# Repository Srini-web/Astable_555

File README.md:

# Astable Vibrator using NE555 timer module
The design of an astable vibrator using the Autodesk Eagle software. The module is designed using the NE555 timer module. It also features an external Voltage regulator to filter out the 5 to 5.5 voltage received. The interface primarily features:

+ STM-NE555 timer
+ LM7805 fixed voltage IC regulator
+ DCJ0202 DC power jack (2.1mm)

These are followed by other basic electronic components like resistors, Capacitors, and LEDs.

## Schematic
The schematic design includes all the elements of the astable vibrator circuit including a pull-up circuit for the input voltage.

### ERC

## Placement (Layout)

## Routing

#### Groundpour

### DRC

## Manufacture View

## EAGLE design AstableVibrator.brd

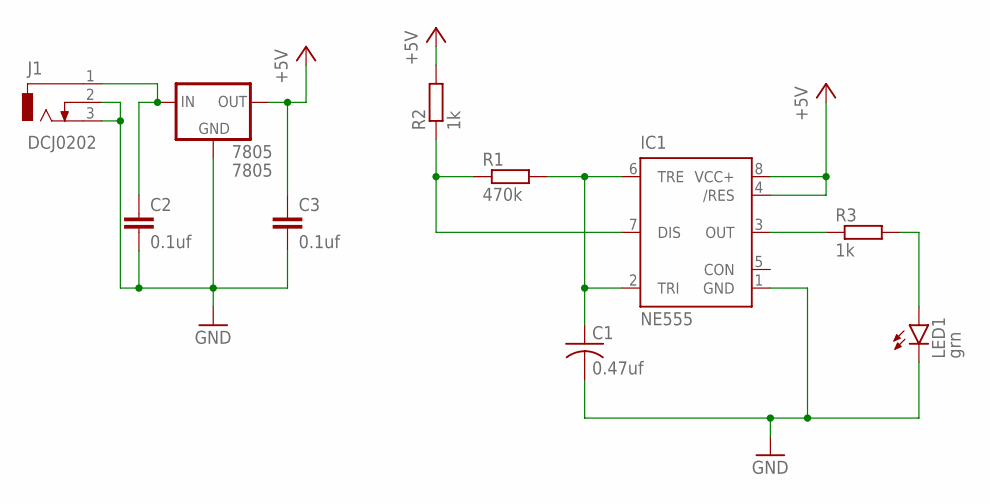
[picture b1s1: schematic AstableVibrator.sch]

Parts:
7805: 7805; 78MXXS
C1: 0.47uf; C025_050-045X075
C2, C3: 0.1uf; C025-050X050
IC1: NE555; DIL-08
J1: DCJ0202
LED1: grn; LED5MM
R1: 470k; 0411/15
R2, R3: 1k; 0411/15

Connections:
+5V: 7805.OUT, C3.1, IC1.4 (/RES), IC1.8 (VCC+), R2.2
GND: 7805.GND, C1.2, C2.2, C3.2, IC1.1 (GND), J1.2, J1.3, LED1.K (C)
unnamed: IC1.3 (OUT), R3.1
unnamed: LED1.A, R3.2
unnamed: IC1.7 (DIS), R1.1, R2.1
unnamed: C1.1, IC1.2 (TRI), IC1.6 (TRE), R1.2
unnamed: 7805.IN, C2.1, J1.1

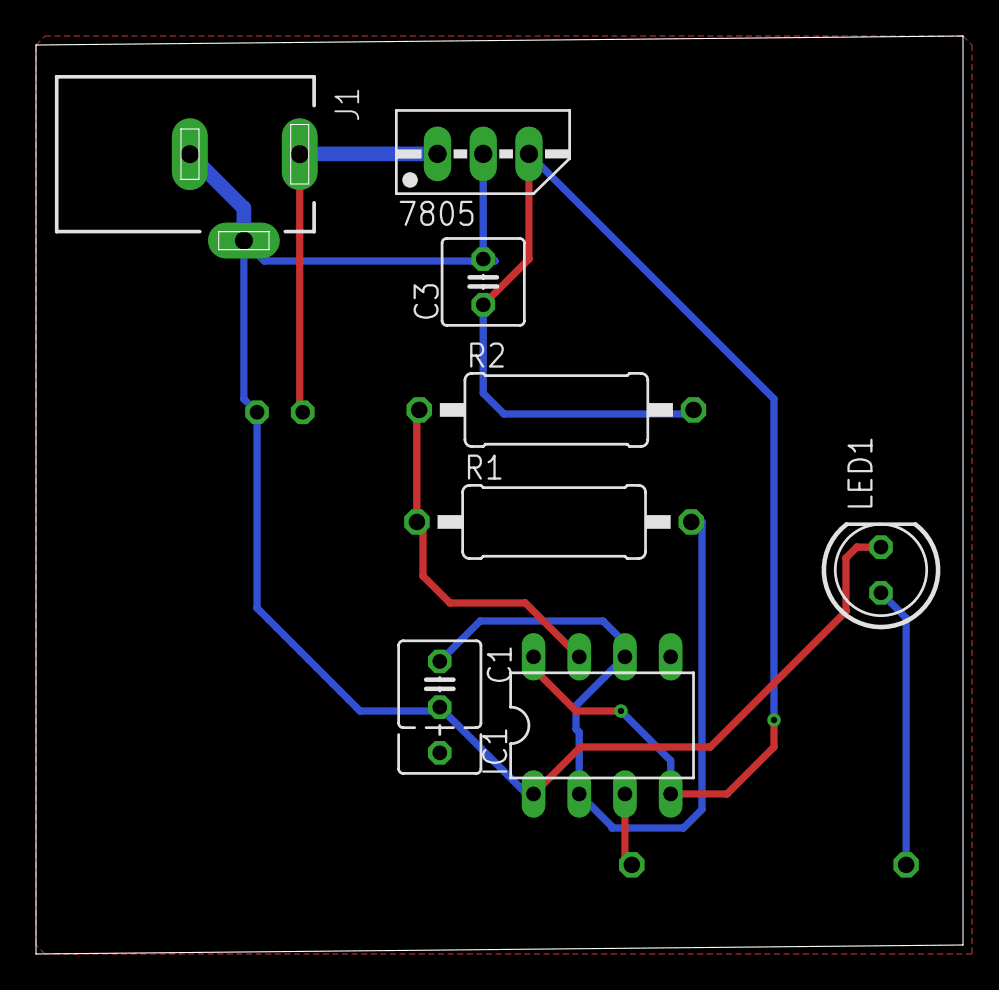
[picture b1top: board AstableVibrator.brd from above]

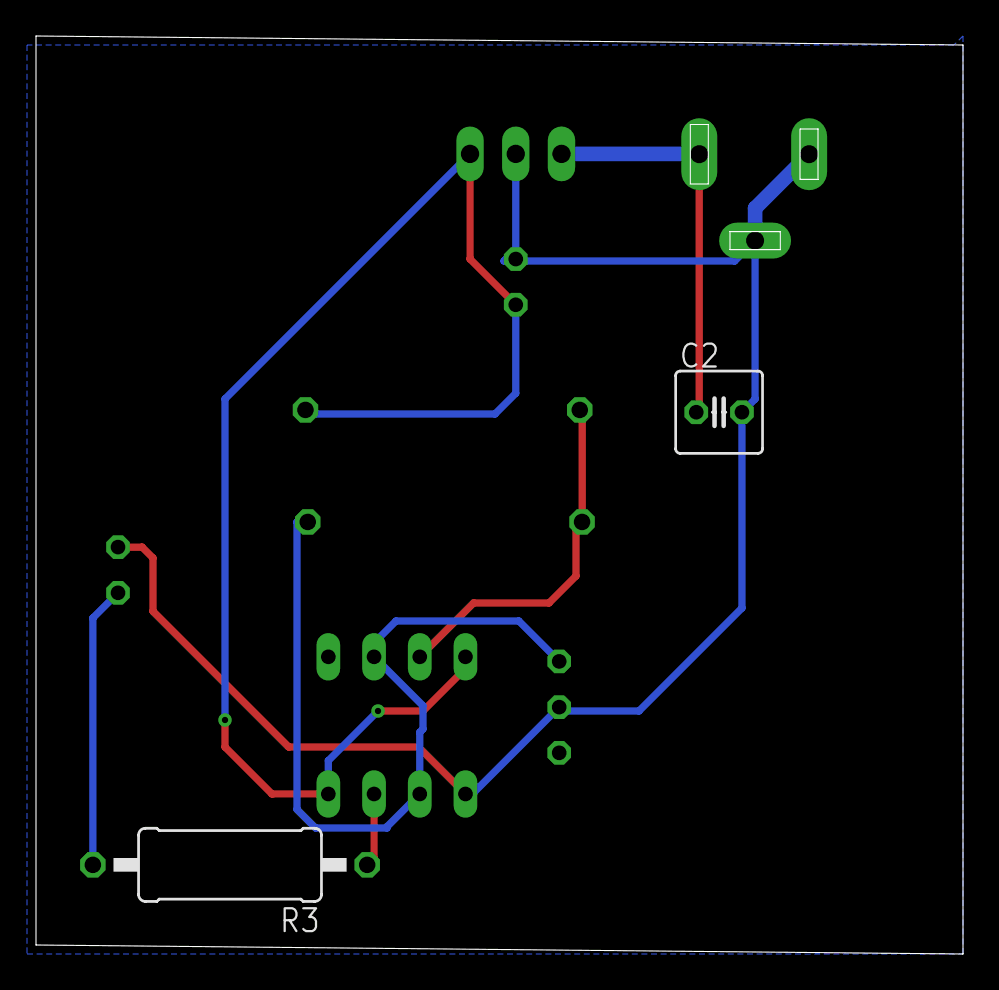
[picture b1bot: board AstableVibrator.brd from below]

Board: 2 copper layers, 51.5 x 51.0 mm, 10 parts (2 on the bottom side), 7 nets.

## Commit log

2024-01-15 File Upload
